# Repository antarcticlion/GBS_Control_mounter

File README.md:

# GBS_Control_mounter
[GBS-Control](https://github.com/ramapcsx2/gbs-control) Mounting plate for GBS-8200/8220

これはテスト中のプロダクトです。不具合が残っているかもしれません。  

----
# Note for Rev 0.6
外形を調整、クロックジェネレータモジュールを追加。
  
外形  

RGB MULTICONV と一緒にスタックした例  

クロックジェネレータモジュール(秋月電子通商 AE-Si5351A-Bを使用)

# Note for Rev 0.4
HD-VC9900をサポート

# Note for Rev 0.3
This is a product under test. There may be some bugs left.  
これはテスト中のプロダクトです。不具合が残っているかもしれません。  

# ライセンス

CC BY-SA 4.0とMITライセンスのデュアルライセンスとします。

クリエイティブコモンズ　表示 - 継承 4.0 国際 (CC BY-SA 4.0)

https://creativecommons.org/licenses/by-sa/4.0/  
https://creativecommons.org/licenses/by-sa/4.0/legalcode

Copyright 2019-2020 @antarcticlion

Permission is hereby granted, free of charge, to any person obtaining a copy of this software and associated documentation files (the "Software"), to deal in the Software without restriction, including without limitation the rights to use, copy, modify, merge, publish, distribute, sublicense, and/or sell copies of the Software, and to permit persons to whom the Software is furnished to do so, subject to the following conditions:

The above copyright notice and this permission notice shall be included in all copies or substantial portions of the Software.

THE SOFTWARE IS PROVIDED "AS IS", WITHOUT WARRANTY OF ANY KIND, EXPRESS OR IMPLIED, INCLUDING BUT NOT LIMITED TO THE WARRANTIES OF MERCHANTABILITY, FITNESS FOR A PARTICULAR PURPOSE AND NONINFRINGEMENT. IN NO EVENT SHALL THE AUTHORS OR COPYRIGHT HOLDERS BE LIABLE FOR ANY CLAIM, DAMAGES OR OTHER LIABILITY, WHETHER IN AN ACTION OF CONTRACT, TORT OR OTHERWISE, ARISING FROM, OUT OF OR IN CONNECTION WITH THE SOFTWARE OR THE USE OR OTHER DEALINGS IN THE SOFTWARE.

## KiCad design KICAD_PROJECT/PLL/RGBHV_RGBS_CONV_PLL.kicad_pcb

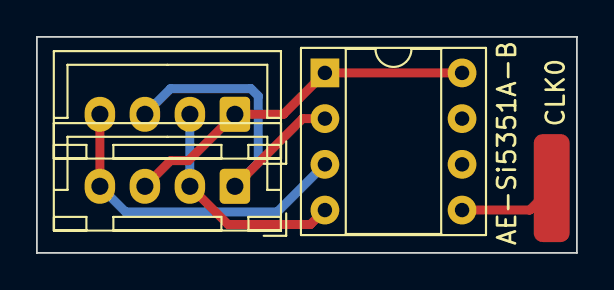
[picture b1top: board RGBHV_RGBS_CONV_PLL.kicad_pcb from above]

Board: 2 copper layers, 30.0 x 12.0 mm, 4 parts (0 on the bottom side), 5 nets.

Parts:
J1: I2C OVERLAY; JST_XH_B4B-XH-A_1x04_P2.50mm_Vertical
J4: CLK0; PAD
J5: I2C GBS; JST_XH_B4B-XH-A_1x04_P2.50mm_Vertical
U1: AE-Si5351A-B; DIP-8_W7.62mm_Socket

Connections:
unnamed: J1.1, J5.3, U1.1, U1.8
unnamed: J1.2, J5.2, U1.4
unnamed: J1.3, J5.1, U1.2
unnamed: J1.4, J5.4, U1.3
unnamed: J4.1, U1.5

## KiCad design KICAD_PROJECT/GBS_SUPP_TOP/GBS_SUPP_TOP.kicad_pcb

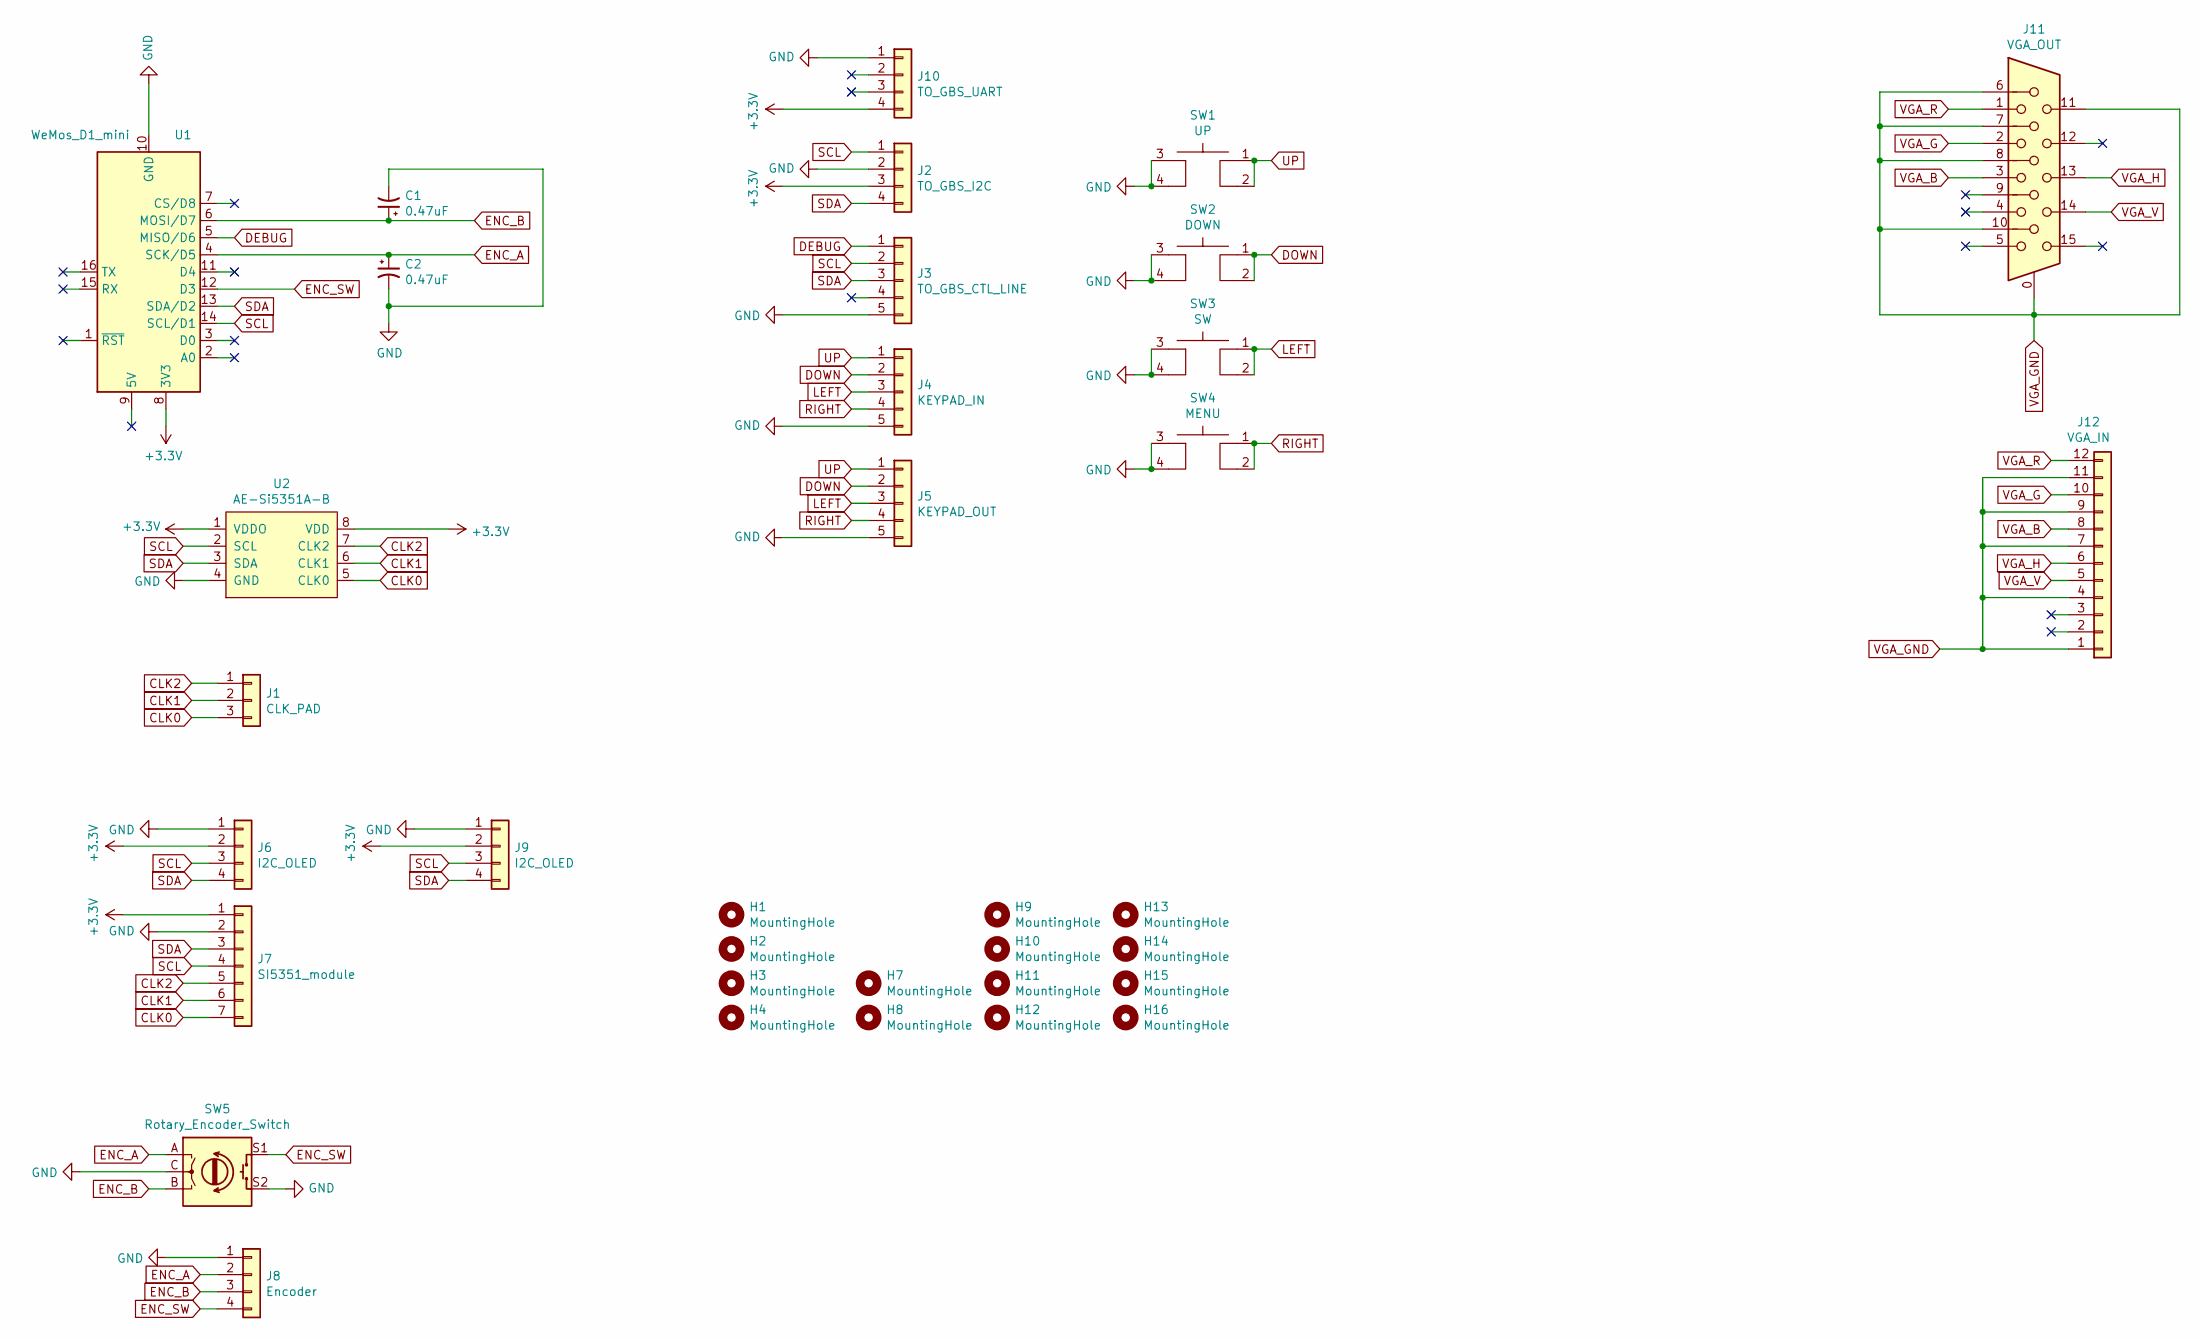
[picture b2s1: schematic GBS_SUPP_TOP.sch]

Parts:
C1, C2: 0.47uF; CP_Radial_D6.3mm_P2.50mm
H1, H2, H3, H4, H9, H10, H11, H12, H13, H14, H15, H16: MountingHole; MountingHole_4.3mm_M4
H7, H8: MountingHole; MountingHole_3.2mm_M3
J1: CLK_PAD; TerminalBlock_Phoenix_PTSM-0,5-3-2.5-H-THR_1x03_P2.50mm_Hor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
J2: TO_GBS_I2C; JST_XH_B4B-XH-A_1x04_P2.50mm_Vertical
J3: TO_GBS_CTL_LINE; JST_XH_B5B-XH-A_1x05_P2.50mm_Vertical
J4: KEYPAD_IN; JST_XH_B5B-XH-A_1x05_P2.50mm_Vertical
J5: KEYPAD_OUT; JST_XH_B5B-XH-A_1x05_P2.50mm_Vertical
J6, J9: I2C_OLED; JST_XH_B4B-XH-A_1x04_P2.50mm_Vertical
J7: SI5351_module; JST_XH_B7B-XH-A_1x07_P2.50mm_Vertical
J8: Encoder; JST_XH_B4B-XH-A_1x04_P2.50mm_Vertical
J10: TO_GBS_UART; JST_XH_B4B-XH-A_1x04_P2.50mm_Vertical
J11: VGA_OUT; DB_15F-VGA_L
J12: VGA_IN; JST_PH_B12B-PH-K_1x12_P2.00mm_Vertical
SW1: UP; SW_TH_Tactile_Omron_B3F-10xx
SW2: DOWN; SW_TH_Tactile_Omron_B3F-10xx
SW3: SW; SW_TH_Tactile_Omron_B3F-10xx
SW4: MENU; SW_TH_Tactile_Omron_B3F-10xx
SW5: Rotary_Encoder_Switch; RotaryEncoder_Alps_EC12E-Switch_Vertical_H20mm
U1: WeMos_D1_mini; WEMOS_D1_mini_light
U2: AE-Si5351A-B; DIP-8_W7.62mm_Socket

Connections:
+3V3: J2.3, J6.2, J7.1, J9.2, J10.4, U1.8 (3V3), U2.1 (VDDO), U2.8 (VDD); also elsewhere on the board
CLK0: J1.3, J7.7, U2.5 (CLK0)
CLK1: J1.2, J7.6, U2.6 (CLK1)
CLK2: J1.1, J7.5, U2.7 (CLK2)
DEBUG: J3.1, U1.5 (MISO/D6)
DOWN: J4.2, J5.2, SW2.1, SW2.2
ENC_A: C2.1, J8.2, SW5.A, U1.4 (SCK/D5)
ENC_B: C1.1, J8.3, SW5.B, U1.6 (MOSI/D7)
ENC_SW: J8.4, SW5.S1, U1.12 (D3)
GND: C1.2, C2.2, J2.2, J3.5, J4.5, J5.5, J6.1, J7.2, J8.1, J9.1, J10.1, SW1.3, SW1.4, SW2.3, SW2.4, SW3.3, SW3.4, SW4.3, SW4.4, SW5.C, SW5.S2, U1.10 (GND), U2.4 (GND); also elsewhere on the board
LEFT: J4.3, J5.3, SW3.1, SW3.2
RIGHT: J4.4, J5.4, SW4.1, SW4.2
SCL: J2.1, J3.2, J6.3, J7.4, J9.3, U1.14 (SCL/D1), U2.2 (SCL); also elsewhere on the board
SDA: J2.4, J3.3, J6.4, J7.3, J9.4, U1.13 (SDA/D2), U2.3 (SDA); also elsewhere on the board
UP: J4.1, J5.1, SW1.1, SW1.2
VGA_B: J11.3, J12.8
VGA_G: J11.2, J12.10
VGA_GND: J11.0, J11.6, J11.7, J11.8, J11.10, J11.11, J12.1, J12.4, J12.7, J12.9, J12.11
VGA_H: J11.13, J12.6
VGA_R: J11.1, J12.12
VGA_V: J11.14, J12.5

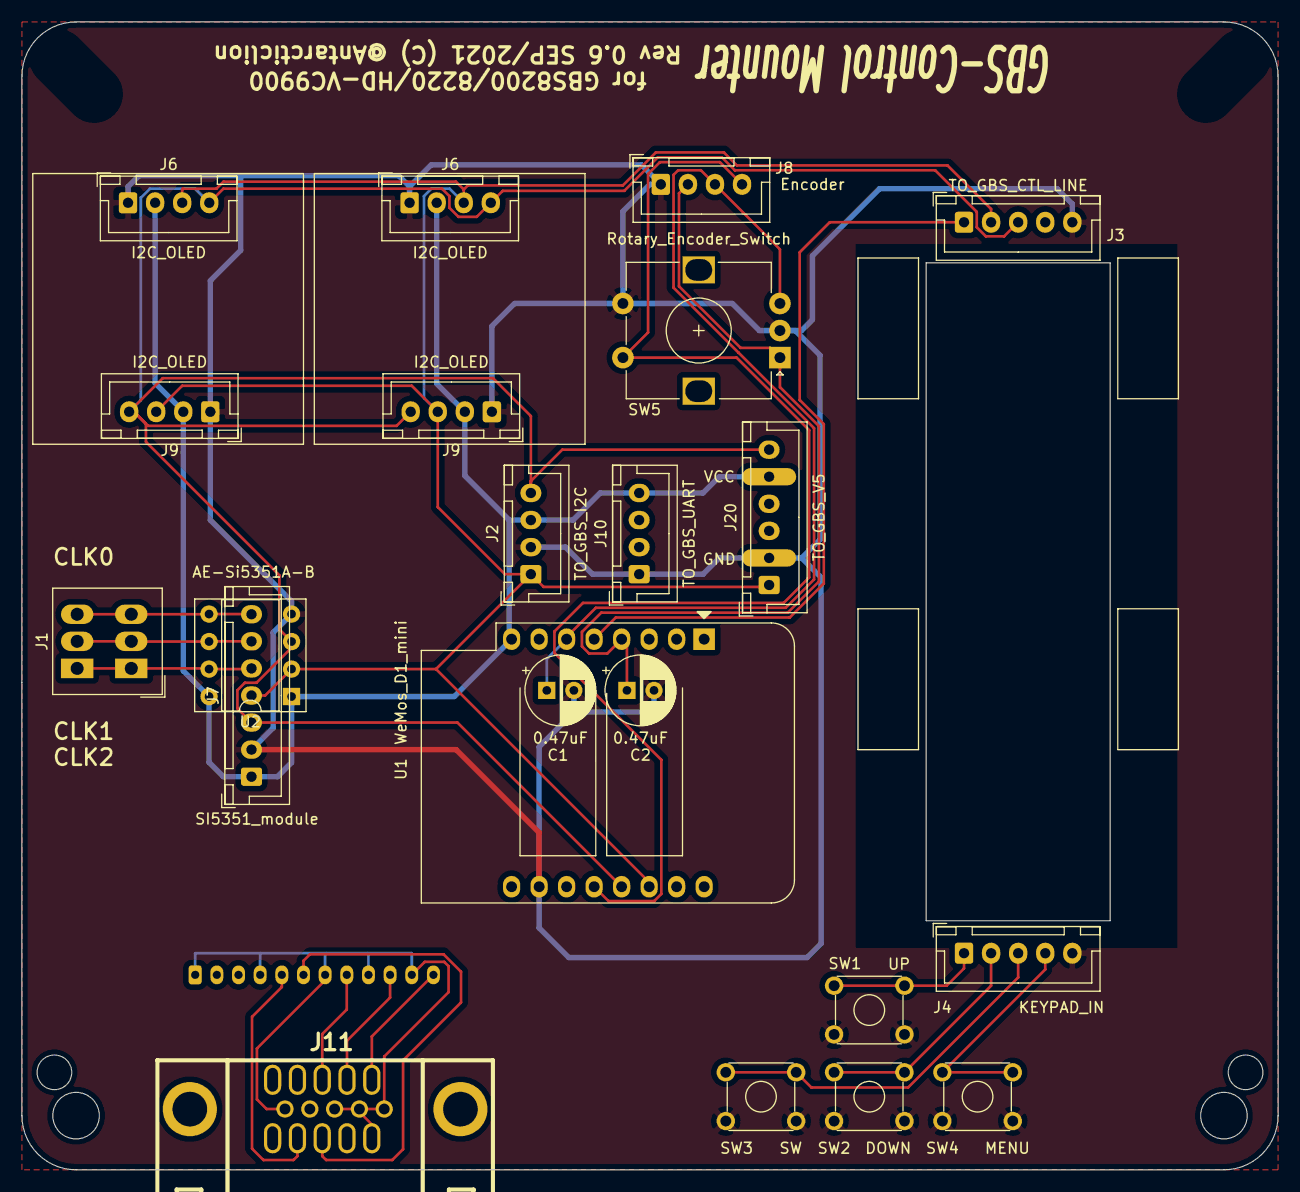
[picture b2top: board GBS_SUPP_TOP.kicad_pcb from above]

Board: 2 copper layers, 116.0 x 106.0 mm, 37 parts (1 on the bottom side), 21 nets.

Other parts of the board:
J6#2, J9#2: I2C_OLED; JST_XH_B4B-XH-A_1x04_P2.50mm_Vertical
J20: TO_GBS_V5; JST_XH_B6B-XH-A_1x06_P2.50mm_Vertical

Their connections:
+3V3: J6#2.2, J9#2.2, J20.5; also elsewhere on the board
GND: J6#2.1, J9#2.1, J20.2; also elsewhere on the board
SCL: J6#2.3, J9#2.3, J20.1; also elsewhere on the board
SDA: J6#2.4, J9#2.4, J20.6; also elsewhere on the board

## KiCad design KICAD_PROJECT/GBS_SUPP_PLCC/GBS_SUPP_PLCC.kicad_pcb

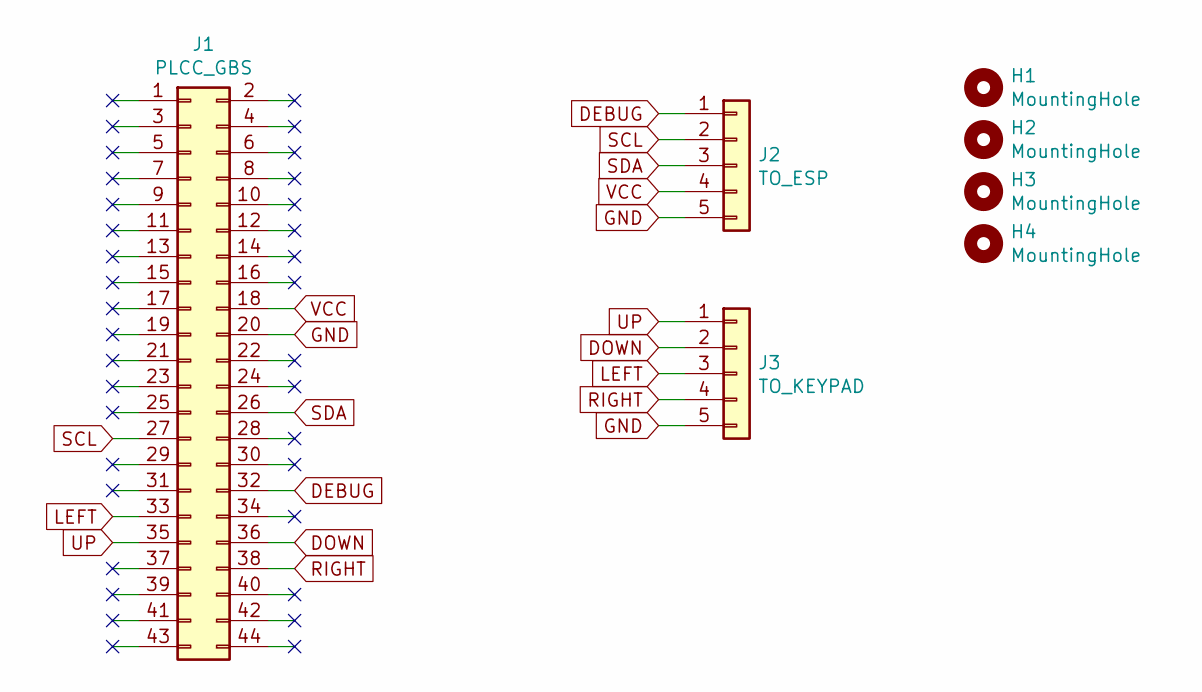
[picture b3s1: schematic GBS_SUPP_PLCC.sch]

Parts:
H1, H2, H3, H4: MountingHole; MountingHole_3.2mm_M3
J1: PLCC_GBS; PLCC-44_THT-Socket
J2: TO_ESP; JST_XH_B5B-XH-A_1x05_P2.50mm_Vertical
J3: TO_KEYPAD; JST_XH_B5B-XH-A_1x05_P2.50mm_Vertical

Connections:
DEBUG: J1.32, J2.1
DOWN: J1.36, J3.2
GND: J1.20, J2.5, J3.5
LEFT: J1.33, J3.3
RIGHT: J1.38, J3.4
SCL: J1.27, J2.2
SDA: J1.26, J2.3
UP: J1.35, J3.1
VCC: J1.18, J2.4

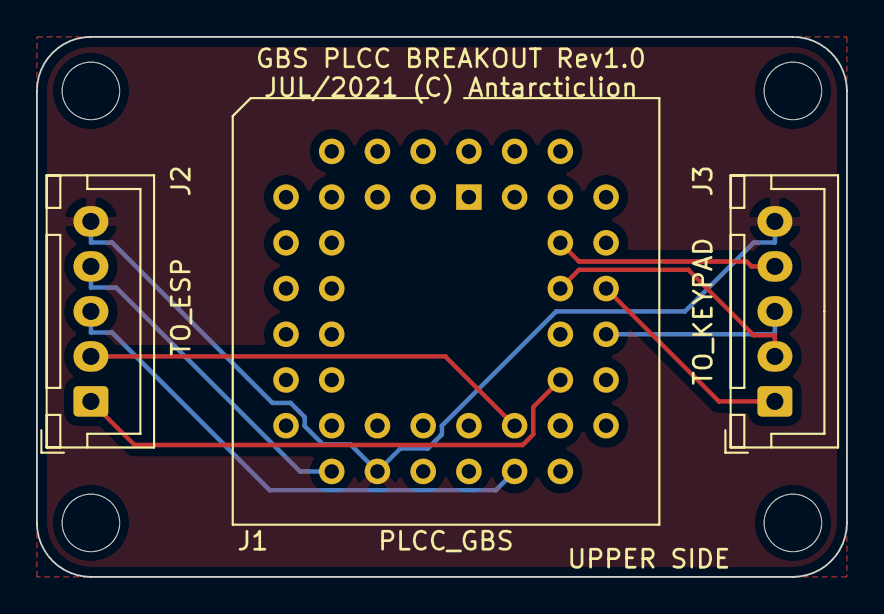
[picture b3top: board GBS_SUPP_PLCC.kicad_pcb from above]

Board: 2 copper layers, 45.0 x 30.0 mm, 7 parts (0 on the bottom side), 9 nets.

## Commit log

2021-07-26 Rev 0.3
    Initial upload
2021-07-26 Initial Upload
2021-07-26 Rev 0.3
2021-08-03 Rev0.3A
    Fix PLCC Board mounting hole problem.
2021-08-03 Rev0.3A
2021-08-18 Rev 0.4
    Support HD-VC9900
2021-08-18 Rev0.4
2022-10-03 Rev 0.6
2022-10-03 Clockgen module Rev2.0
2022-10-03 Clockgen module Rev 2.0
2022-10-03 Cleckgen Rev2.0
